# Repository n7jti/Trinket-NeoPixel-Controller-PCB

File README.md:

# Trinket-NeoPixel-Controller-PCB
A small PCB that uses Adafruit's best practices to connect to a NeoPixel strand. This is based on the Trinket M0 and used to control Neo-Pixel strands. 

Adafruit invests time and resources providing this open source code,
please support Adafruit and open-source hardware by purchasing
products from Adafruit!

## Parts List
1. Adafruit Trinket M0:  https://www.adafruit.com/product/3500
2. 3-pin screw Terminals: https://www.newark.com/webapp/wcs/stores/servlet/ProductDisplay?catalogId=10001&langId=-1&urlRequestType=Base&partNumber=48Y4480&storeId=10194
3. 470 Ohm Resistors: https://www.adafruit.com/product/2781
4. 3v to 5v logic level shifter: https://www.adafruit.com/product/1787
5. 2mm DC connector: https://www.newark.com/webapp/wcs/stores/servlet/ProductDisplay?catalogId=10001&langId=-1&urlRequestType=Base&partNumber=75Y6644&storeId=10194
6. 1000uF Capacitor: https://www.newark.com/webapp/wcs/stores/servlet/ProductDisplay?catalogId=10001&langId=-1&urlRequestType=Base&partNumber=96K9139&storeId=10194

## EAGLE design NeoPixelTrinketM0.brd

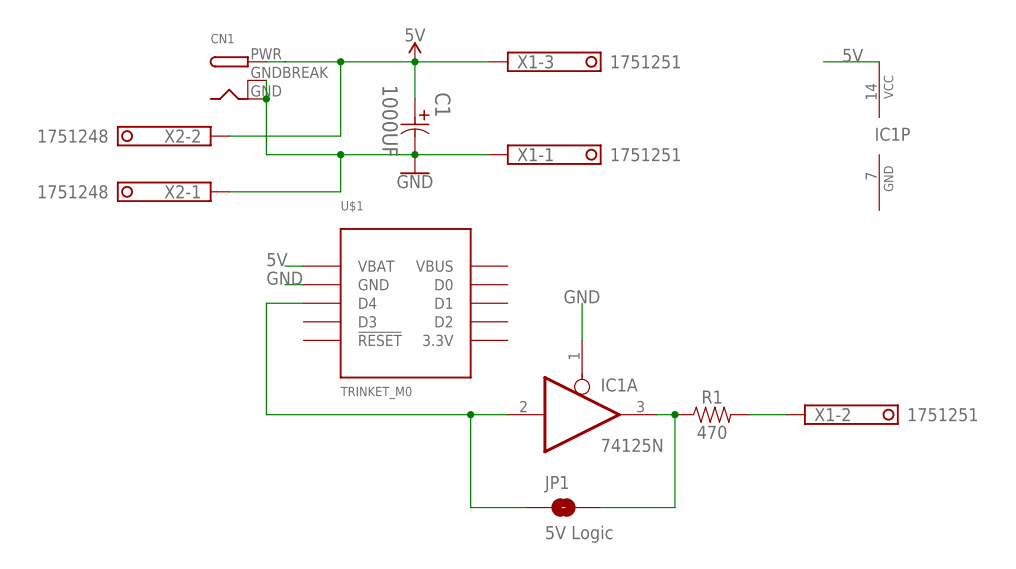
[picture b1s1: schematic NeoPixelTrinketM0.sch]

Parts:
C1: 1000UF; CAPPR350-800X1150
CN1: DCBARRELPTH; DCJACK_2MM_PTH
IC1: 74125N; DIL14
JP1: 5V Logic; SMT-JUMPER_2_NO_SILK_ROUND
R1: 470; AXIAL-0.3
U$1: TRINKET_M0; TRINKET
X1: 1751251
X2: 1751248

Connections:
3.3V: U$1.P$6 (3.3V)
5V: C1.1, CN1.PWR, IC1.14 (VCC), U$1.P$1 (VBAT), X1.3, X2.2
GND: C1.2, CN1.GND, CN1.GNDBREAK, IC1.1 (OE), IC1.7 (GND), U$1.P$2 (GND), X1.1, X2.1
unnamed: IC1.3 (O), JP1.2, R1.P$1 (1)
unnamed: R1.P$2 (2), X1.2
unnamed: IC1.2 (I), JP1.1, U$1.P$3 (D4)
VBUS: U$1.P$10 (VBUS)

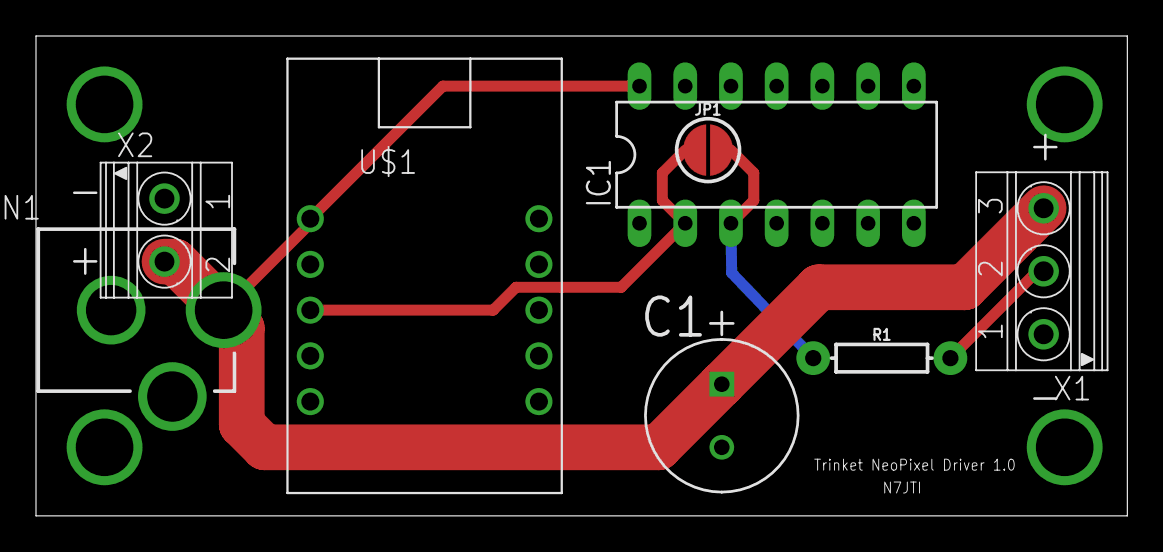
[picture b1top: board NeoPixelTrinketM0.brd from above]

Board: 2 copper layers, 60.6 x 26.7 mm, 8 parts (0 on the bottom side), 5 nets.

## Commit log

2018-09-18 Add the PCB
    Add the schematic and PCB
2018-09-23 Some STL Files for 3D Printing an enclosure

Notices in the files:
parts and their libraries:
SparkFun-Resistors: Licensing: Creative Commons ShareAlike 4.0 International - https://creativecommons.org/licenses/by-sa/4.0
